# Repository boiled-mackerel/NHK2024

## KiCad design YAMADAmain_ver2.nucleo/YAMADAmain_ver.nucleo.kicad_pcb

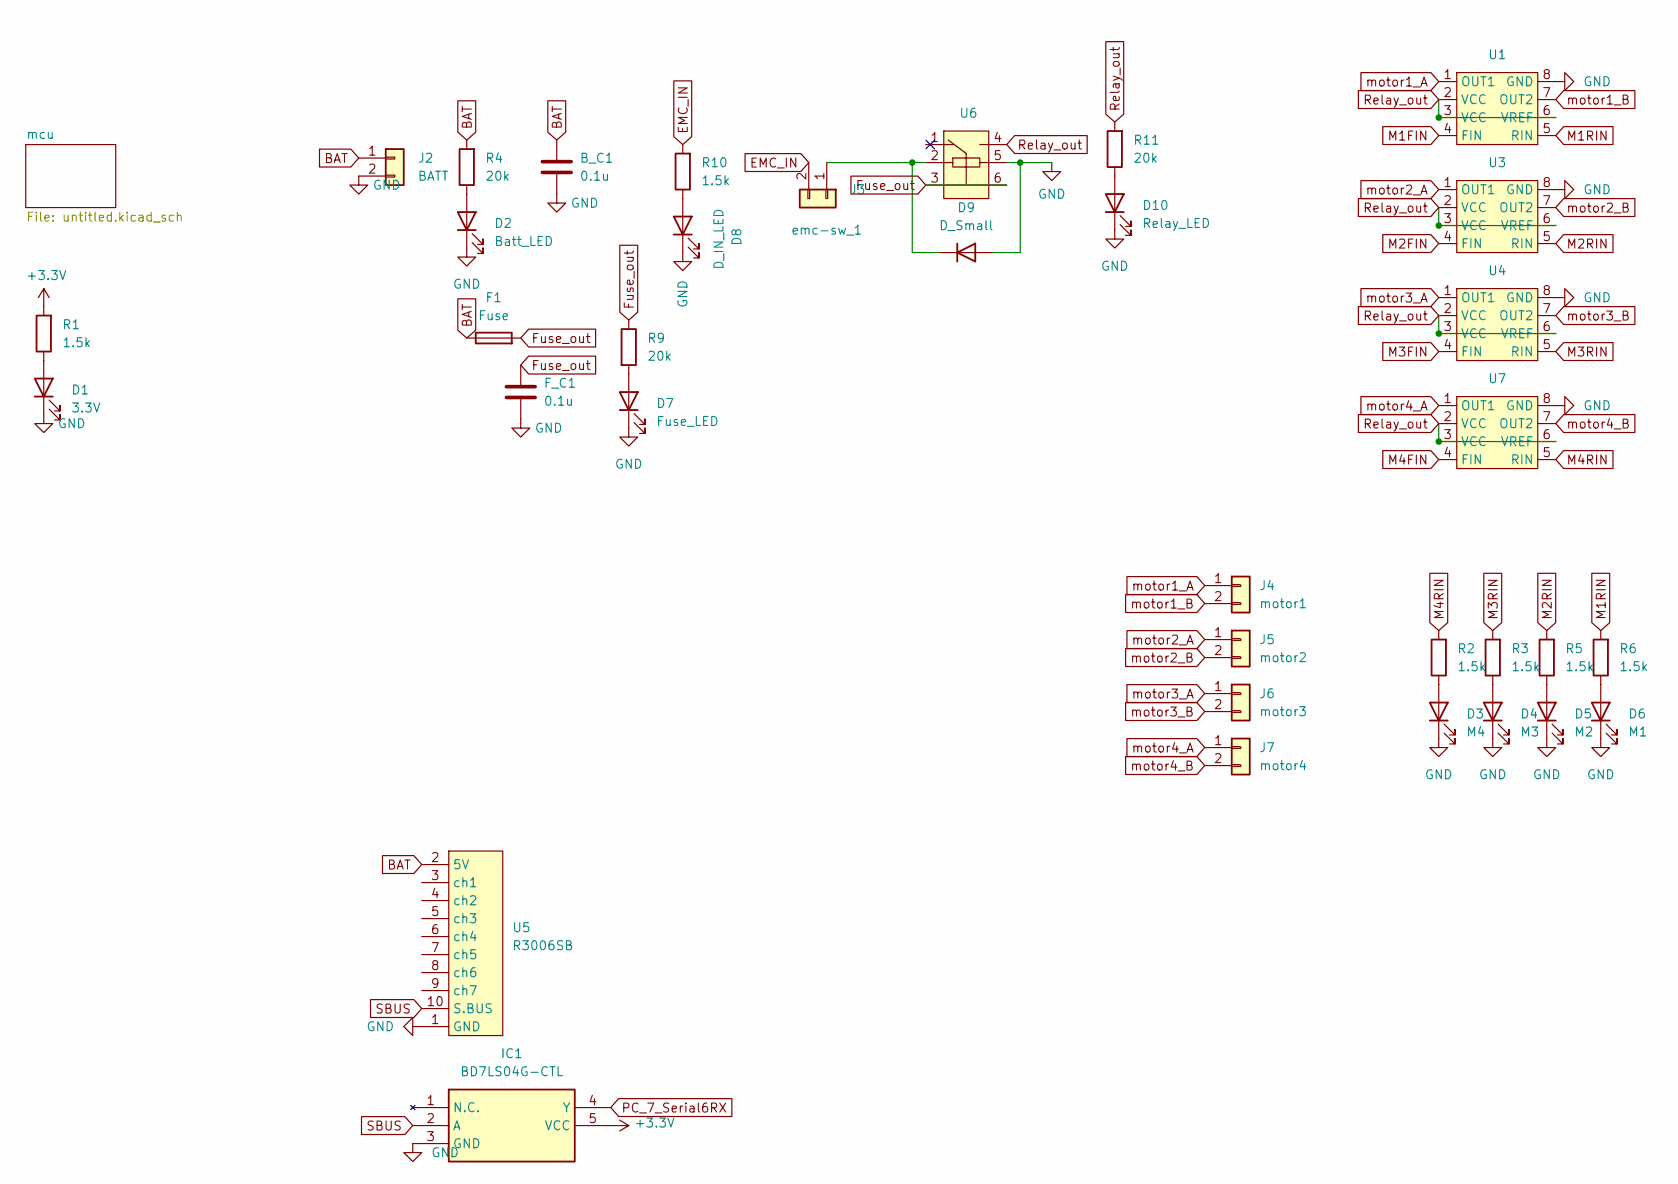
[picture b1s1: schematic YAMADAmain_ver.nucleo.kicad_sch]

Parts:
B_C1: 0.1u; C_0805_2012
D1: 3.3V; LED_D3.0mm
D2: Batt_LED; LED_D3.0mm
D3: M4; LED_D3.0mm
D4: M3; LED_D3.0mm
D5: M2; LED_D3.0mm
D6: M1; LED_D3.0mm
D7: Fuse_LED; LED_D3.0mm
D8: D_IN_LED; LED_D3.0mm
D9: D_Small; D_SOD-123
D10: Relay_LED; LED_D3.0mm
F1: Fuse; FuseHolder_Carfuse
F_C1: 0.1u; C_0805_2012Metric_Pad1.18x1.45mm_HandSolder
IC1: BD7LS04G-CTL; SOT95P280X125-5N; Manufacturer_Part_Number BD7LS04G-CTL
J2: BATT; POWER_PAD
J3: emc-sw_1; JST_XA_S02B-XASK-1_1x02_P2.50mm_Horizontal
J4: motor1; JST_GH_BM02B-GHS-TBT_1x02-1MP_P1.25mm_Vertical
J5: motor2; JST_GH_BM02B-GHS-TBT_1x02-1MP_P1.25mm_Vertical
J6: motor3; JST_GH_BM02B-GHS-TBT_1x02-1MP_P1.25mm_Vertical
J7: motor4; JST_GH_BM02B-GHS-TBT_1x02-1MP_P1.25mm_Vertical
R1, R2, R3, R5, R6, R10: 1.5k; R_Axial_DIN0207_L6.3mm_D2.5mm_P7.62mm_Horizontal
R4, R9, R11: 20k; R_Axial_DIN0207_L6.3mm_D2.5mm_P7.62mm_Horizontal
U1, U3, U4, U7: SOP8
U5: R3006SB
U6: Y14H-1C-3DS

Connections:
+3.3V: IC1.5 (VCC), R1.2; also elsewhere on the board
BAT: B_C1.1, F1.1, J2.1, R4.2, U5.2 (5V); also elsewhere on the board
EMC_IN: J3.2, R10.2; also elsewhere on the board
Fuse_out: F1.2, F_C1.1, R9.1, U6.3, U6.6
GND: B_C1.2, D1.1 (K), D2.1 (K), D3.1 (K), D4.1 (K), D5.1 (K), D6.1 (K), D7.1 (K), D8.1 (K), D9.2 (A), D10.1 (K), F_C1.2, IC1.3 (GND), J2.2, U1.8 (GND), U3.8 (GND), U4.8 (GND), U5.1 (GND), U6.5, U7.8 (GND); also elsewhere on the board
M1FIN: U1.4 (FIN); also elsewhere on the board
M1RIN: R6.2, U1.5 (RIN); also elsewhere on the board
M2FIN: U3.4 (FIN); also elsewhere on the board
M2RIN: R5.2, U3.5 (RIN); also elsewhere on the board
M3FIN: U4.4 (FIN); also elsewhere on the board
M3RIN: R3.2, U4.5 (RIN); also elsewhere on the board
M4FIN: U7.4 (FIN); also elsewhere on the board
M4RIN: R2.2, U7.5 (RIN); also elsewhere on the board
unnamed: D1.2 (A), R1.1
unnamed: D2.2 (A), R4.1
unnamed: D3.2 (A), R2.1
unnamed: D4.2 (A), R3.1
unnamed: D5.2 (A), R5.1
unnamed: D6.2 (A), R6.1
unnamed: D7.2 (A), R9.2
unnamed: D8.2 (A), R10.1
unnamed: D9.1 (K), J3.1, U6.2
unnamed: D10.2 (A), R11.1
PC_7_Serial6RX: IC1.4 (Y); also elsewhere on the board
Relay_out: R11.2, U1.2 (VCC), U1.3 (VCC), U1.6 (VREF), U3.2 (VCC), U3.3 (VCC), U3.6 (VREF), U4.2 (VCC), U4.3 (VCC), U4.6 (VREF), U6.4, U7.2 (VCC), U7.3 (VCC), U7.6 (VREF)
SBUS: IC1.2 (A), U5.10 (S.BUS)
motor1_A: J4.1, U1.1 (OUT1)
motor1_B: J4.2, U1.7 (OUT2)
motor2_A: J5.1, U3.1 (OUT1)
motor2_B: J5.2, U3.7 (OUT2)
motor3_A: J6.1, U4.1 (OUT1)
motor3_B: J6.2, U4.7 (OUT2)
motor4_A: J7.1, U7.1 (OUT1)
motor4_B: J7.2, U7.7 (OUT2)

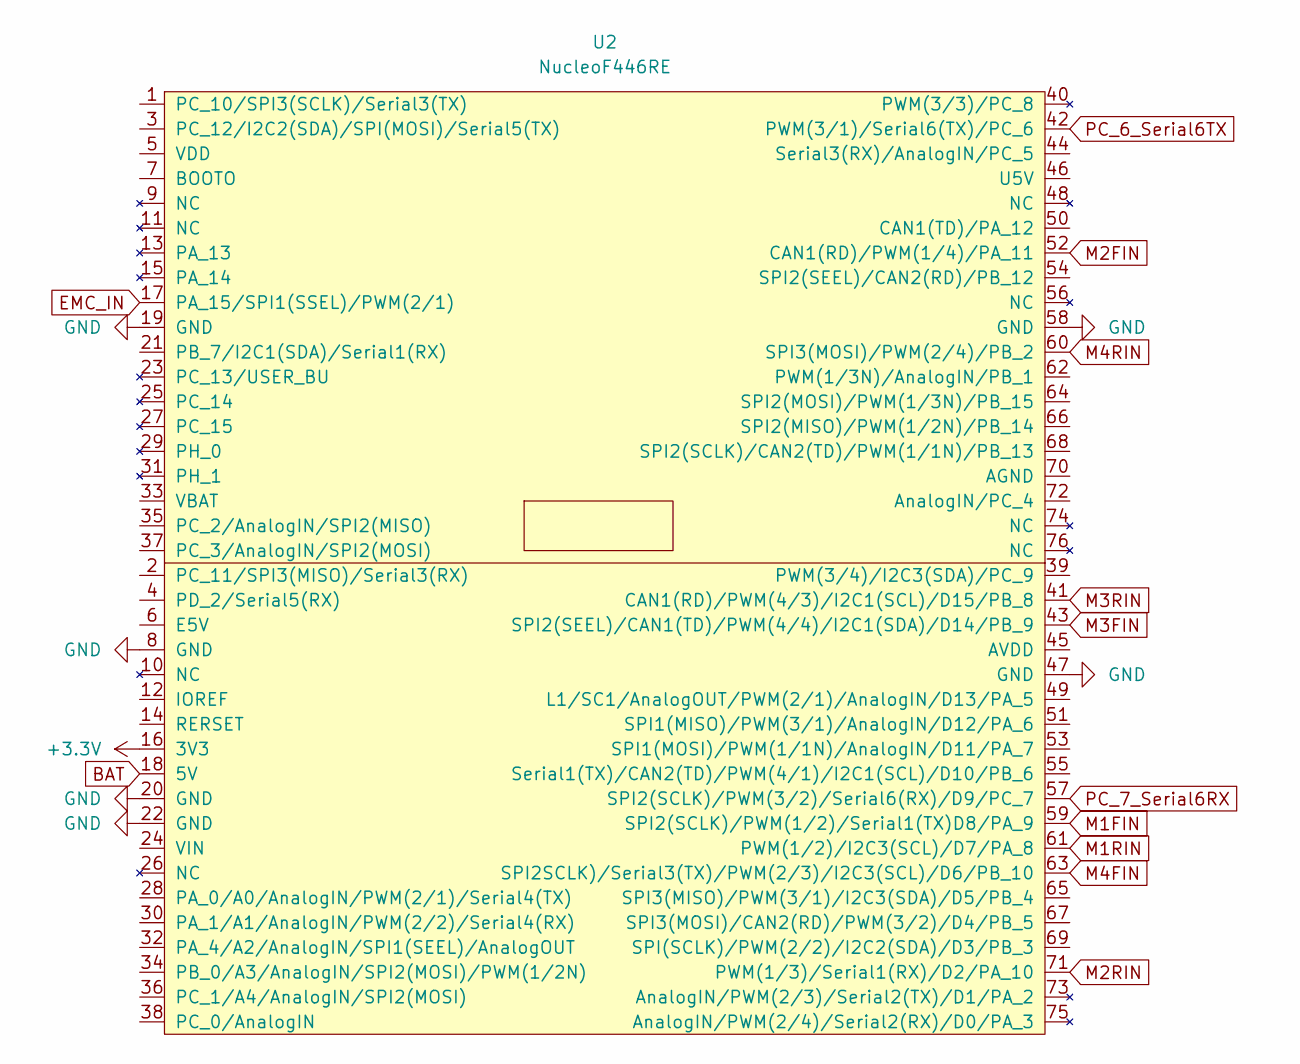
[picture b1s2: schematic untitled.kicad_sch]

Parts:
U2: NucleoF446RE; Nucleo64Board_F446RE

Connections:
+3.3V: U2.16 (3V3); also elsewhere on the board
BAT: U2.18 (5V); also elsewhere on the board
EMC_IN: U2.17 (PA_15/SPI1(SSEL)/PWM(2/1)); also elsewhere on the board
GND: U2.8 (GND), U2.19 (GND), U2.20 (GND), U2.22 (GND), U2.47 (GND), U2.58 (GND); also elsewhere on the board
M1FIN: U2.59 (SPI2(SCLK)/PWM(1/2)/Serial1(TX)D8/PA_9); also elsewhere on the board
M1RIN: U2.61 (PWM(1/2)/I2C3(SCL)/D7/PA_8); also elsewhere on the board
M2FIN: U2.52 (CAN1(RD)/PWM(1/4)/PA_11); also elsewhere on the board
M2RIN: U2.71 (PWM(1/3)/Serial1(RX)/D2/PA_10); also elsewhere on the board
M3FIN: U2.43 (SPI2(SEEL)/CAN1(TD)/PWM(4/4)/I2C1(SDA)/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); also elsewhere on the board
M3RIN: U2.41 (CAN1(RD)/PWM(4/3)/I2C1(SCL)/D15/PB_8); also elsewhere on the board
M4FIN: U2.63 (SPI2SCLK)/Serial3(TX)/PWM(2/3)/I2C3(SCL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); also elsewhere on the board
M4RIN: U2.60 (SPI3(MOSI)/PWM(2/4)/PB_2); also elsewhere on the board
PC_6_Serial6TX: U2.42 (PWM(3/1)/Serial6(TX)/PC_6)
PC_7_Serial6RX: U2.57 (SPI2(SCLK)/PWM(3/2)/Serial6(RX)/D9/PC_7); also elsewhere on the board

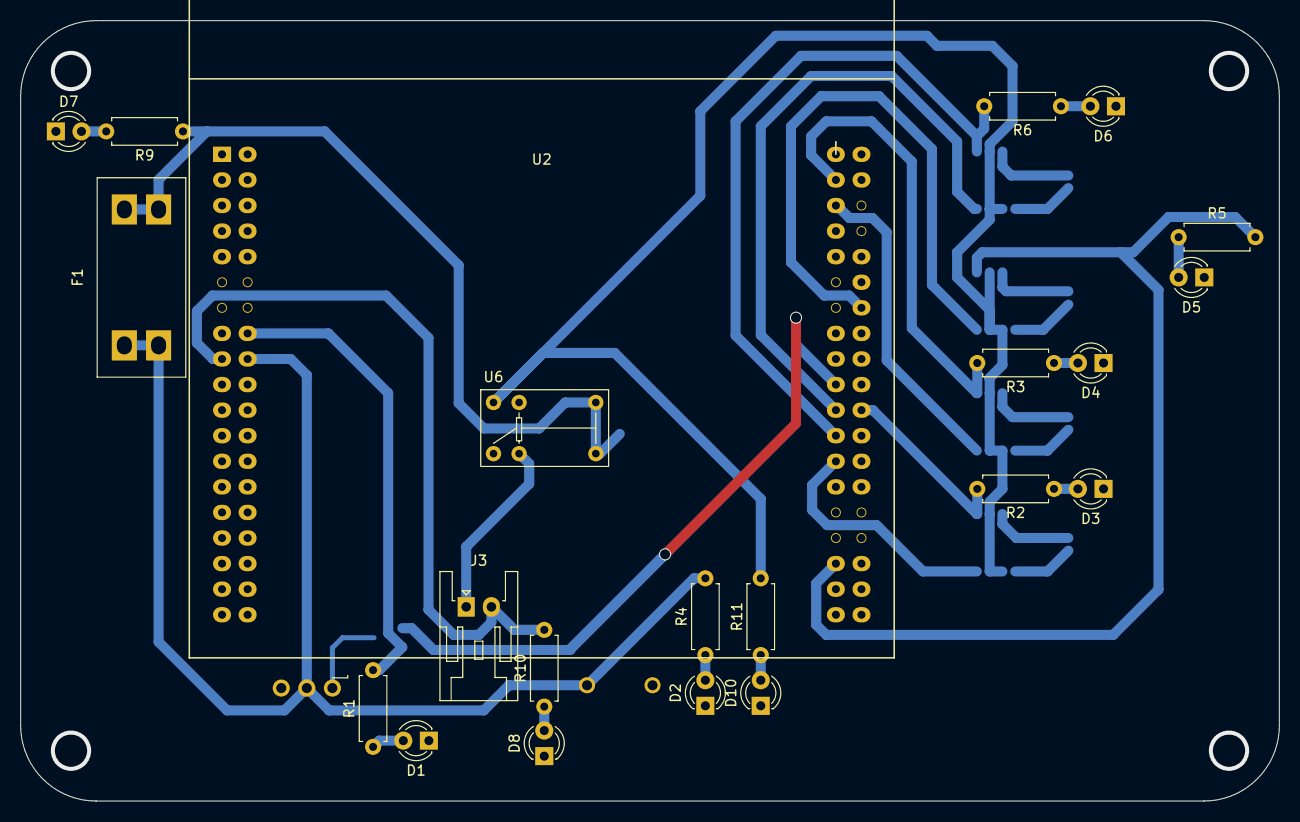
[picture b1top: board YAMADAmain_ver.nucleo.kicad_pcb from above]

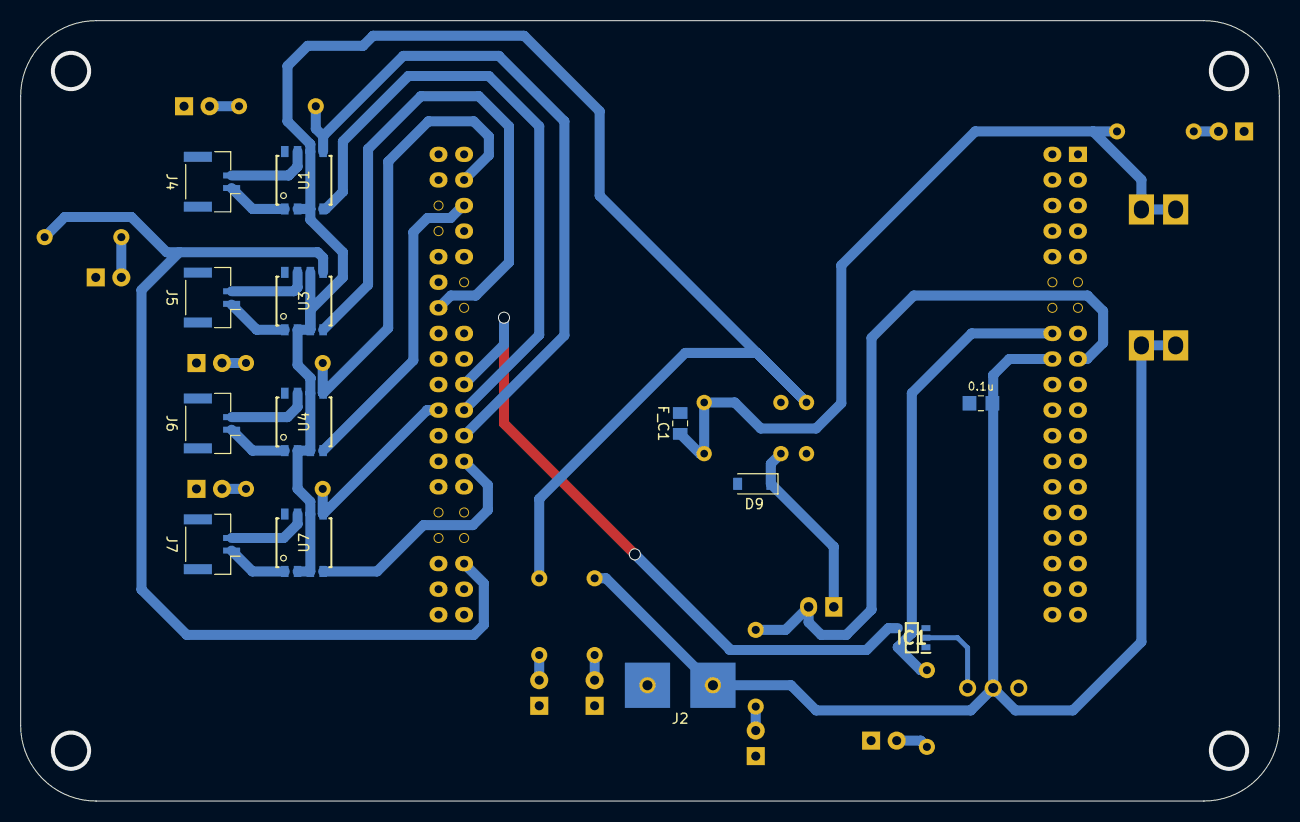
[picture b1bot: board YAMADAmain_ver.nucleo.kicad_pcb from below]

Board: 2 copper layers, 125.0 x 77.5 mm, 36 parts (13 on the bottom side), 34 nets.

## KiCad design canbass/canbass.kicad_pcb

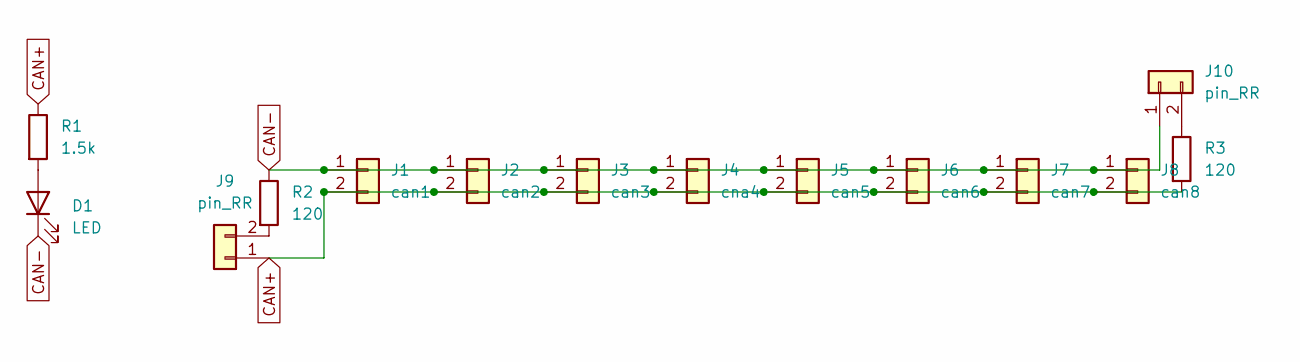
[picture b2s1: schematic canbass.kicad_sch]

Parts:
D1: LED; LED_0603_1608Metric_Pad1.05x0.95mm_HandSolder
J1: can1; JST_GH_SM02B-GHS-TB_1x02-1MP_P1.25mm_Horizontal
J2: can2; JST_GH_SM02B-GHS-TB_1x02-1MP_P1.25mm_Horizontal
J3: can3; JST_GH_SM02B-GHS-TB_1x02-1MP_P1.25mm_Horizontal
J4: cna4; JST_GH_SM02B-GHS-TB_1x02-1MP_P1.25mm_Horizontal
J5: can5; JST_GH_SM02B-GHS-TB_1x02-1MP_P1.25mm_Horizontal
J6: can6; JST_GH_SM02B-GHS-TB_1x02-1MP_P1.25mm_Horizontal
J7: can7; JST_GH_SM02B-GHS-TB_1x02-1MP_P1.25mm_Horizontal
J8: can8; JST_GH_SM02B-GHS-TB_1x02-1MP_P1.25mm_Horizontal
J9, J10: pin_RR; PinSocket_1x02_P2.54mm_Vertical
R1: 1.5k; R_0805_2012Metric_Pad1.20x1.40mm_HandSolder
R2: 120; R_0805_2012Metric_Pad1.20x1.40mm_HandSolder
R3: 120; R_0805_2012Metric

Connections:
CAN+: J1.2, J2.2, J3.2, J4.2, J5.2, J6.2, J7.2, J8.2, J9.1, R1.1, R3.2
CAN-: D1.1 (K), J1.1, J2.1, J3.1, J4.1, J5.1, J6.1, J7.1, J8.1, J10.1, R2.1
unnamed: D1.2 (A), R1.2
unnamed: J9.2, R2.2
unnamed: J10.2, R3.1

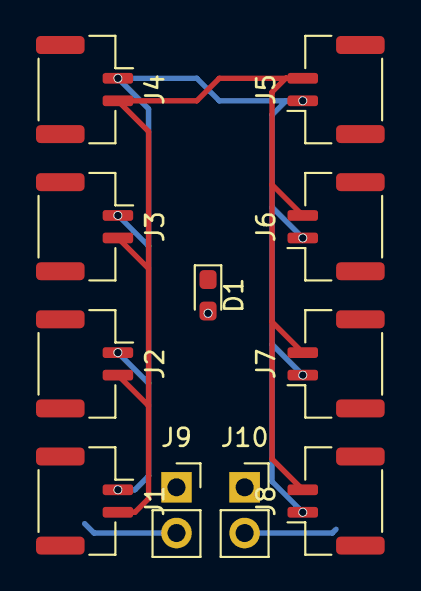
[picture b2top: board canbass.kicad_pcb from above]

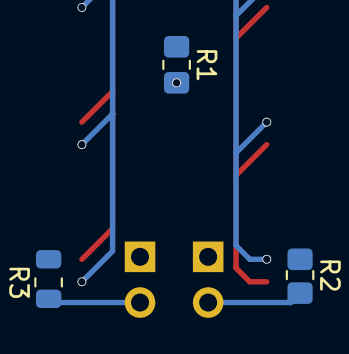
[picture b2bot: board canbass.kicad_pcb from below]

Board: 2 copper layers, 14 parts (3 on the bottom side), 5 nets.

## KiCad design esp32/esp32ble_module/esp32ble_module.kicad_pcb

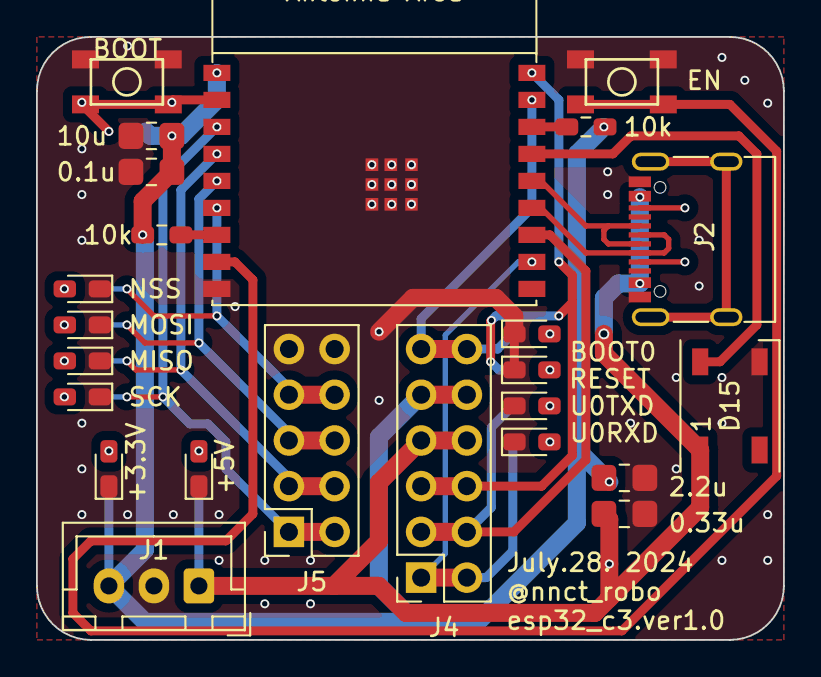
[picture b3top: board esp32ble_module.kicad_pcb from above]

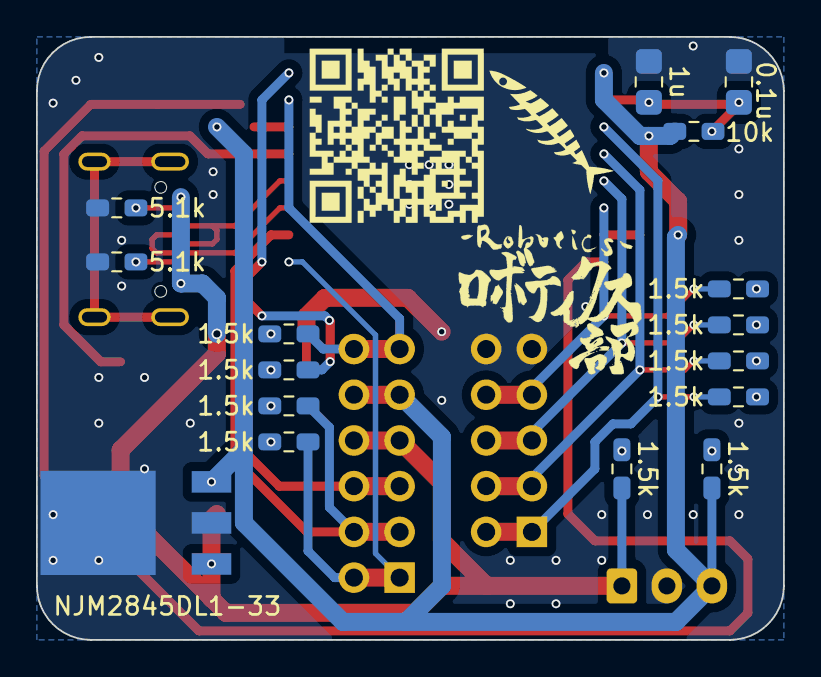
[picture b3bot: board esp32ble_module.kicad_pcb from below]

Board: 2 copper layers, 41.5 x 33.5 mm, 40 parts (16 on the bottom side), 30 nets.

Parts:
C1: 0.33u; C_0805_2012
C2, C6: 0.1u; C_0805_2012
C3: 1u; C_0805_2012
C4: 2.2u; C_0805_2012
C5: 10u; C_0805_2012
D1: +5V; LED_0603_1608
D2: +3.3V; LED_0603_1608
D3: SCK; LED_0603_1608
D4: NSS; LED_0603_1608
D5: MISO; LED_0603_1608
D6: MOSI; LED_0603_1608
D7: U0RXD; LED_0603_1608
D8: U0TXD; LED_0603_1608
D9: BOOT0; LED_0603_1608
D10: RESET; LED_0603_1608
D15: WS2812B; LED_WS2812B_PLCC4_5.0x5.0mm_P3.2mm
J1: power; JST_XH_B3B-XH-A_1x03_P2.50mm_Vertical
J2: USB_C_Receptacle_USB2.0; USB_C_Receptacle_G-Switch_GT-USB-7010ASV
J4: Conn_02x06_Counter_Clockwise; PinSocket_2x06_P2.54mm_Vertical
J5: Conn_02x05_Counter_Clockwise; PinSocket_2x05_P2.54mm_Vertical
R1, R2, R3, R4, R5, R6, R7, R8, R9, R10: 1.5k; R_0603_1608
R15, R16: 5.1k; R_0603_1608
R17, R20, R21: 10k; R_0603_1608
U2: NJM2845DL1-33
U5, U7: SW_DP3T; tact_sw_smd_skrpabe10
U6: ESP32-C3-WROOM-02

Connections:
+3.3V: C4.1, C5.2, C6.2, J1.3, J4.9, J4.10, R2.1, R17.1, R20.2, R21.2, U2.3 (Vout), U6.1 (3V3)
+5V: C1.1, D15.1 (VDD), J1.1, J2.A4 (VBUS), J2.A9 (VBUS), J2.B4 (VBUS), J2.B9 (VBUS), J4.7, J4.8, R1.1, U2.1 (Vin)
BOOT0: J4.11, J4.12, R9.1, U6.17 (GPIO1/ADC1_CH1/XTAL_32K_N)
D+: J2.A6 (D+), J2.B6 (D+), U6.14 (GPIO19/USB_D+)
D-: J2.A7 (D-), J2.B7 (D-), U6.13 (GPIO18/USB_D-)
GND: C1.2, C2.2, C3.2, C4.2, C5.1, C6.1, D1.1 (K), D2.1 (K), D3.1 (K), D4.1 (K), D5.1 (K), D6.1 (K), D7.1 (K), D8.1 (K), D9.1 (K), D10.1 (K), D15.3 (VSS), J1.2, J2.A1 (GND), J2.A12 (GND), J2.B1 (GND), J2.B12 (GND), J5.9, J5.10, R15.2, R16.2, U2.2 (GND), U5.1, U5.3, U6.9 (GND), U6.19 (GND), U7.2, U7.4
LED_DIN: D15.4 (DIN), U6.15 (GPIO3/ADC1_CH3)
MISO: J5.3, J5.4, R5.1, U6.4 (GPIO5/ADC2_CH0)
MOSI: J5.5, J5.6, R6.1, U6.5 (GPIO6)
NSS: J5.7, J5.8, R4.1, U6.6 (GPIO7)
unnamed: D1.2 (A), R1.2
unnamed: D2.2 (A), R2.2
unnamed: D3.2 (A), R3.2
unnamed: D4.2 (A), R4.2
unnamed: D5.2 (A), R5.2
unnamed: D6.2 (A), R6.2
unnamed: D7.2 (A), R7.2
unnamed: D8.2 (A), R8.2
unnamed: D9.2 (A), R9.2
unnamed: D10.2 (A), R10.2
unnamed: J2.A5 (CC1), R15.1
unnamed: J2.B5 (CC2), R16.1
unnamed: C2.1, C3.1, R17.2, U5.2, U5.4, U6.2 (EN/CHIP_PU)
unnamed: R20.1, U6.16 (GPIO2/ADC1_CH2)
unnamed: R21.1, U6.7 (GPIO8)
unnamed: U6.8 (GPIO9), U7.1, U7.3
RESET: J4.5, J4.6, R10.1, U6.18 (GPIO0/ADC1_CH0/XTAL_32K_P)
SCK: J5.1, J5.2, R3.1, U6.3 (GPIO4/ADC1_CH4)
U0RXD: J4.1, J4.2, R7.1, U6.11 (GPIO20/U0RXD)
U0TXD: J4.3, J4.4, R8.1, U6.12 (GPIO21/U0TXD)

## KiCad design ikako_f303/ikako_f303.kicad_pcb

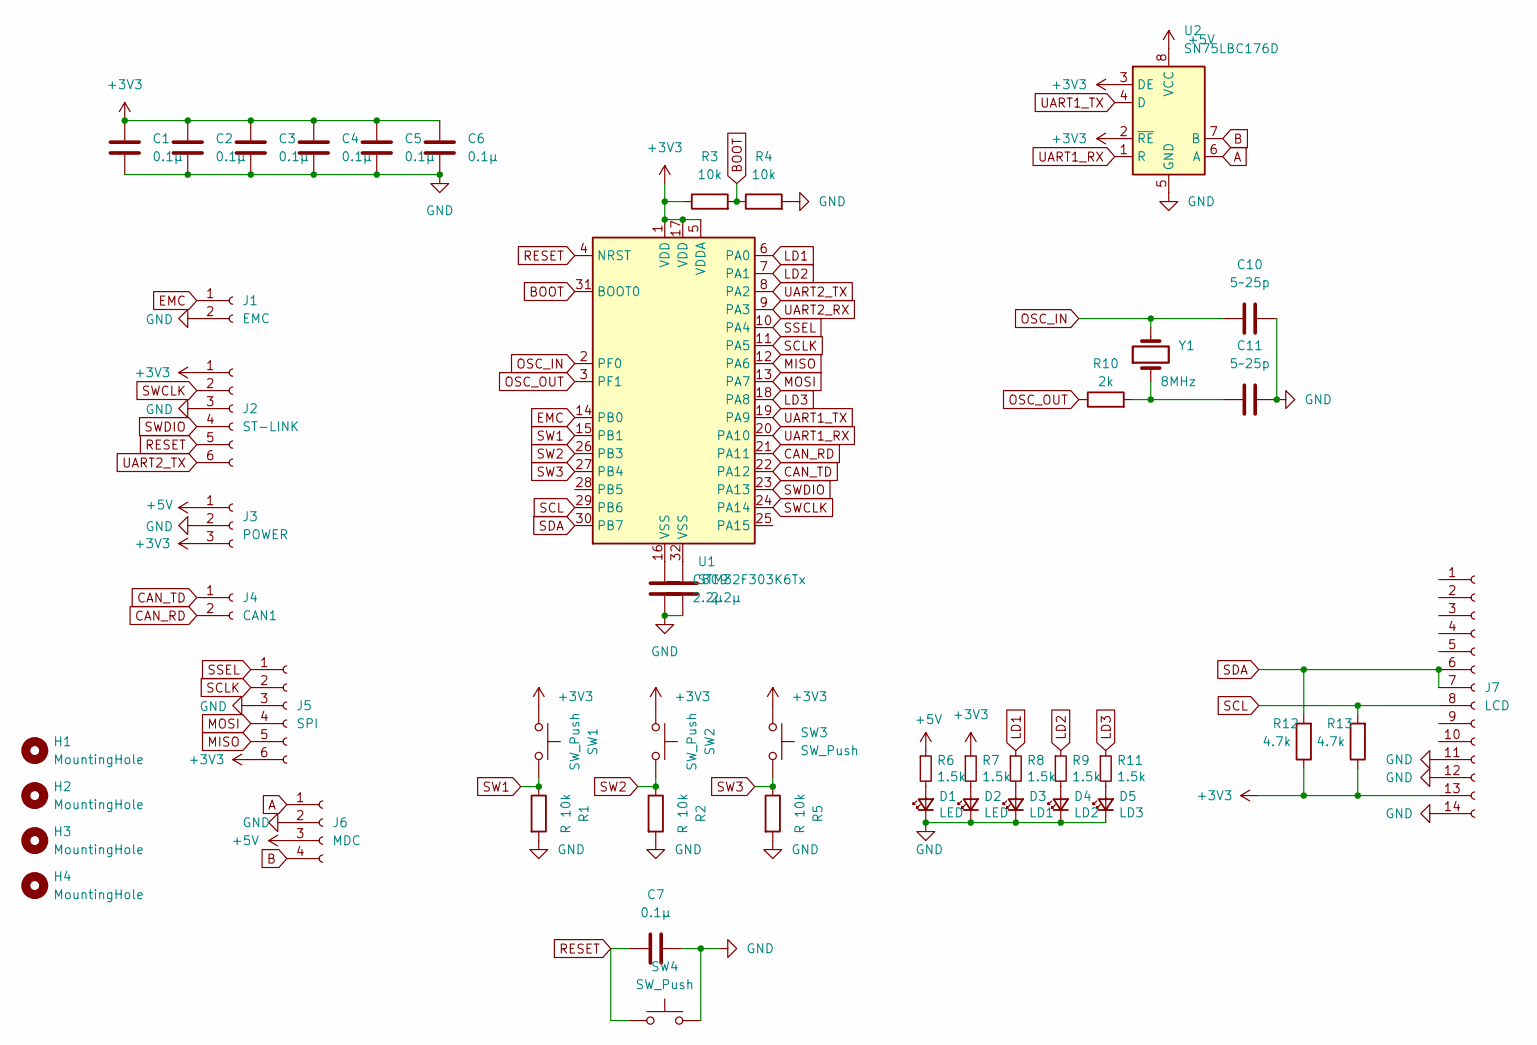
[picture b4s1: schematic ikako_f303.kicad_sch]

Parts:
C1, C2, C3, C4, C5, C6, C7: 0.1µ; C_0504_1310Metric_Pad0.83x1.28mm_HandSolder
C8, C9: 2.2µ; C_1206_3216Metric_Pad1.33x1.80mm_HandSolder
C10, C11: 5~25p; C_0805_2012Metric_Pad1.18x1.45mm_HandSolder
D1, D2: LED; LED_0603_1608Metric_Pad1.05x0.95mm_HandSolder
D3: LD1; LED_0603_1608Metric_Pad1.05x0.95mm_HandSolder
D4: LD2; LED_0603_1608Metric_Pad1.05x0.95mm_HandSolder
D5: LD3; LED_0603_1608Metric_Pad1.05x0.95mm_HandSolder
H1, H2, H3, H4: MountingHole; MountingHole_3.2mm_M3_Pad_Via
J1: EMC; JST_XA_S02B-XASK-1_1x02_P2.50mm_Horizontal
J2: ST-LINK; JST_XA_S06B-XASK-1_1x06_P2.50mm_Horizontal
J3: POWER; JST_XA_S03B-XASK-1_1x03_P2.50mm_Horizontal
J4: CAN1; JST_XA_S02B-XASK-1_1x02_P2.50mm_Horizontal
J5: SPI; PinSocket_1x06_P2.54mm_Horizontal
J6: MDC; JST_XA_S04B-XASK-1_1x04_P2.50mm_Horizontal
J7: LCD; PinSocket_1x14_P2.54mm_Vertical
R1, R2, R5: R 10k; R_0805_2012Metric_Pad1.20x1.40mm_HandSolder
R3, R4: 10k; R_0805_2012Metric_Pad1.20x1.40mm_HandSolder
R6, R7, R8, R9, R11: 1.5k; R_0805_2012Metric_Pad1.20x1.40mm_HandSolder
R10: 2k; R_0805_2012Metric_Pad1.20x1.40mm_HandSolder
R12, R13: 4.7k; R_0805_2012Metric_Pad1.20x1.40mm_HandSolder
SW1, SW2, SW3, SW4: SW_Push; SW_PUSH_6mm
U1: STM32F303K6Tx; LQFP-32_7x7mm_P0.8mm
U2: SN75LBC176D; DIP-8_W7.62mm
Y1: 8MHz; Resonator-2Pin_W10.0mm_H5.0mm

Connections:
+3V3: C1.1, C2.1, C3.1, C4.1, C5.1, C6.1, J2.1, J3.3, J5.6, J7.13, R3.1, R7.1, R12.1, R13.1, SW1.1, SW2.1, SW3.1, U1.1 (VDD), U1.5 (VDDA), U1.17 (VDD), U2.2 (~RE), U2.3 (DE)
+5V: J3.1, J6.3, R6.1, U2.8 (VCC)
A: J6.1, U2.6 (A)
B: J6.4, U2.7 (B)
BOOT: R3.2, R4.1, U1.31 (BOOT0)
CAN_RD: J4.2, U1.21 (PA11)
CAN_TD: J4.1, U1.22 (PA12)
EMC: J1.1, U1.14 (PB0)
GND: C1.2, C2.2, C3.2, C4.2, C5.2, C6.2, C7.2, C8.2, C9.2, C10.2, C11.2, D1.1 (K), D2.1 (K), D3.1 (K), D4.1 (K), D5.1 (K), J1.2, J2.3, J3.2, J5.3, J6.2, J7.11, J7.12, J7.14, R1.2, R2.2, R4.2, R5.2, SW4.2, U2.5 (GND)
LD1: R8.1, U1.6 (PA0)
LD2: R9.1, U1.7 (PA1)
LD3: R11.1, U1.18 (PA8)
MISO: J5.5, U1.12 (PA6)
MOSI: J5.4, U1.13 (PA7)
unnamed: C8.1, U1.16 (VSS)
unnamed: C9.1, U1.32 (VSS)
unnamed: C11.1, R10.2, Y1.1
unnamed: D1.2 (A), R6.2
unnamed: D2.2 (A), R7.2
unnamed: D3.2 (A), R8.2
unnamed: D4.2 (A), R9.2
unnamed: D5.2 (A), R11.2
OSC_IN: C10.1, U1.2 (PF0), Y1.2
OSC_OUT: R10.1, U1.3 (PF1)
RESET: C7.1, J2.5, SW4.1, U1.4 (NRST)
SCL: J7.8, R13.2, U1.29 (PB6)
SCLK: J5.2, U1.11 (PA5)
SDA: J7.6, J7.7, R12.2, U1.30 (PB7)
SSEL: J5.1, U1.10 (PA4)
SW1: R1.1, SW1.2, U1.15 (PB1)
SW2: R2.1, SW2.2, U1.26 (PB3)
SW3: R5.1, SW3.2, U1.27 (PB4)
SWCLK: J2.2, U1.24 (PA14)
SWDIO: J2.4, U1.23 (PA13)
UART1_RX: U1.20 (PA10), U2.1 (R)
UART1_TX: U1.19 (PA9), U2.4 (D)
UART2_RX: U1.9 (PA3)
UART2_TX: J2.6, U1.8 (PA2)

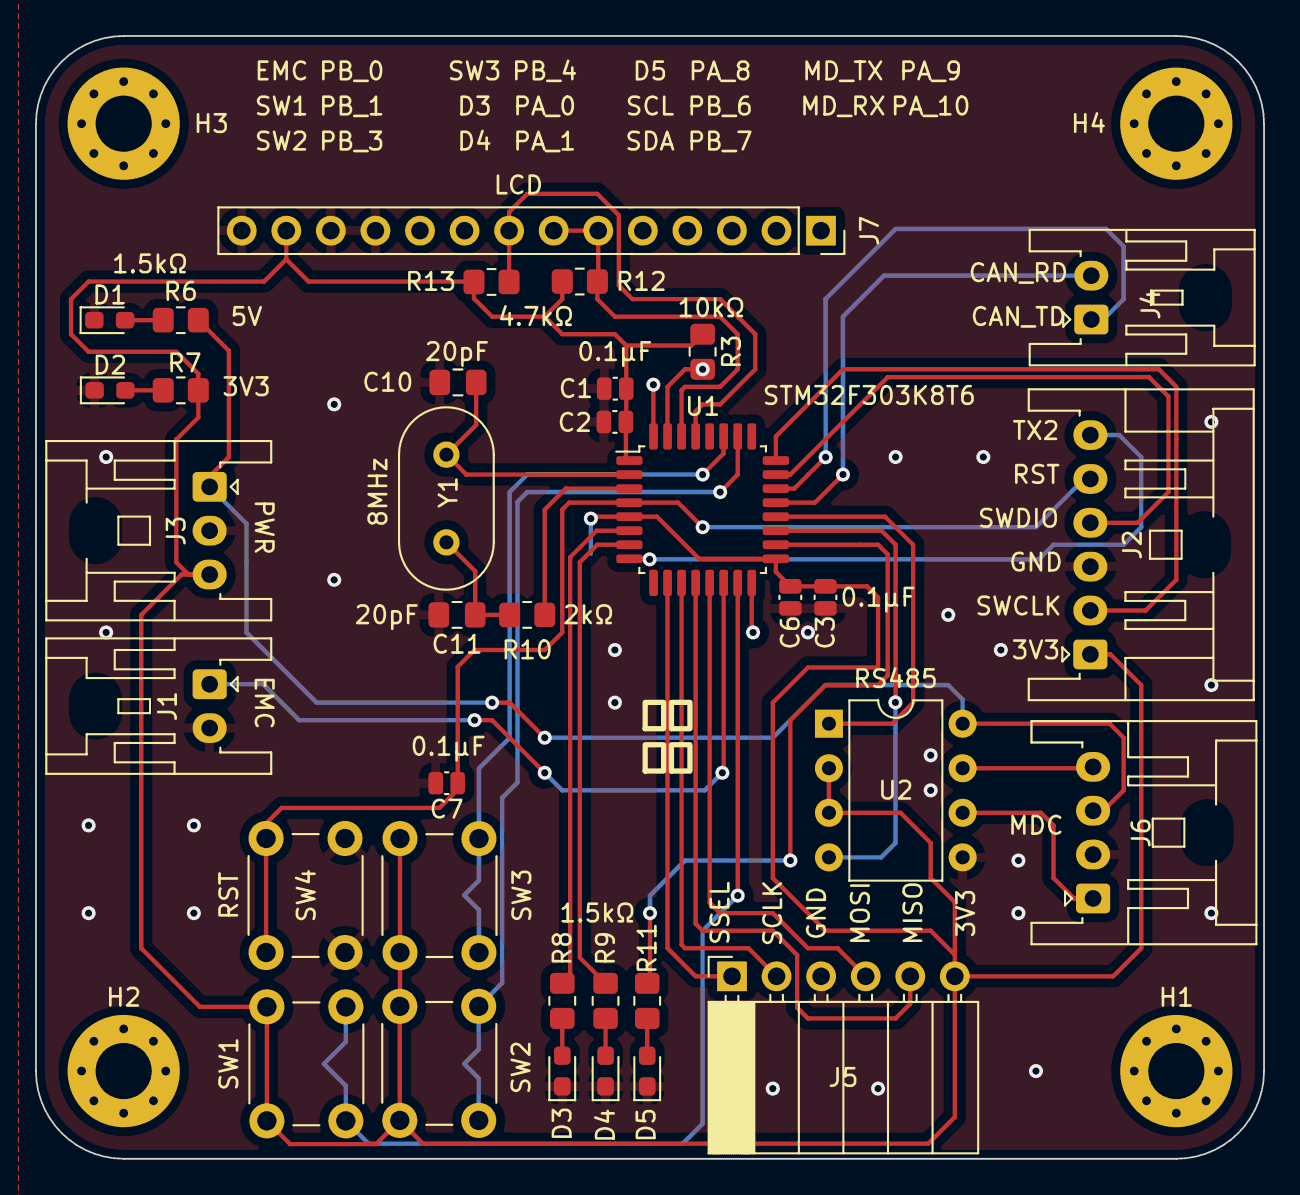
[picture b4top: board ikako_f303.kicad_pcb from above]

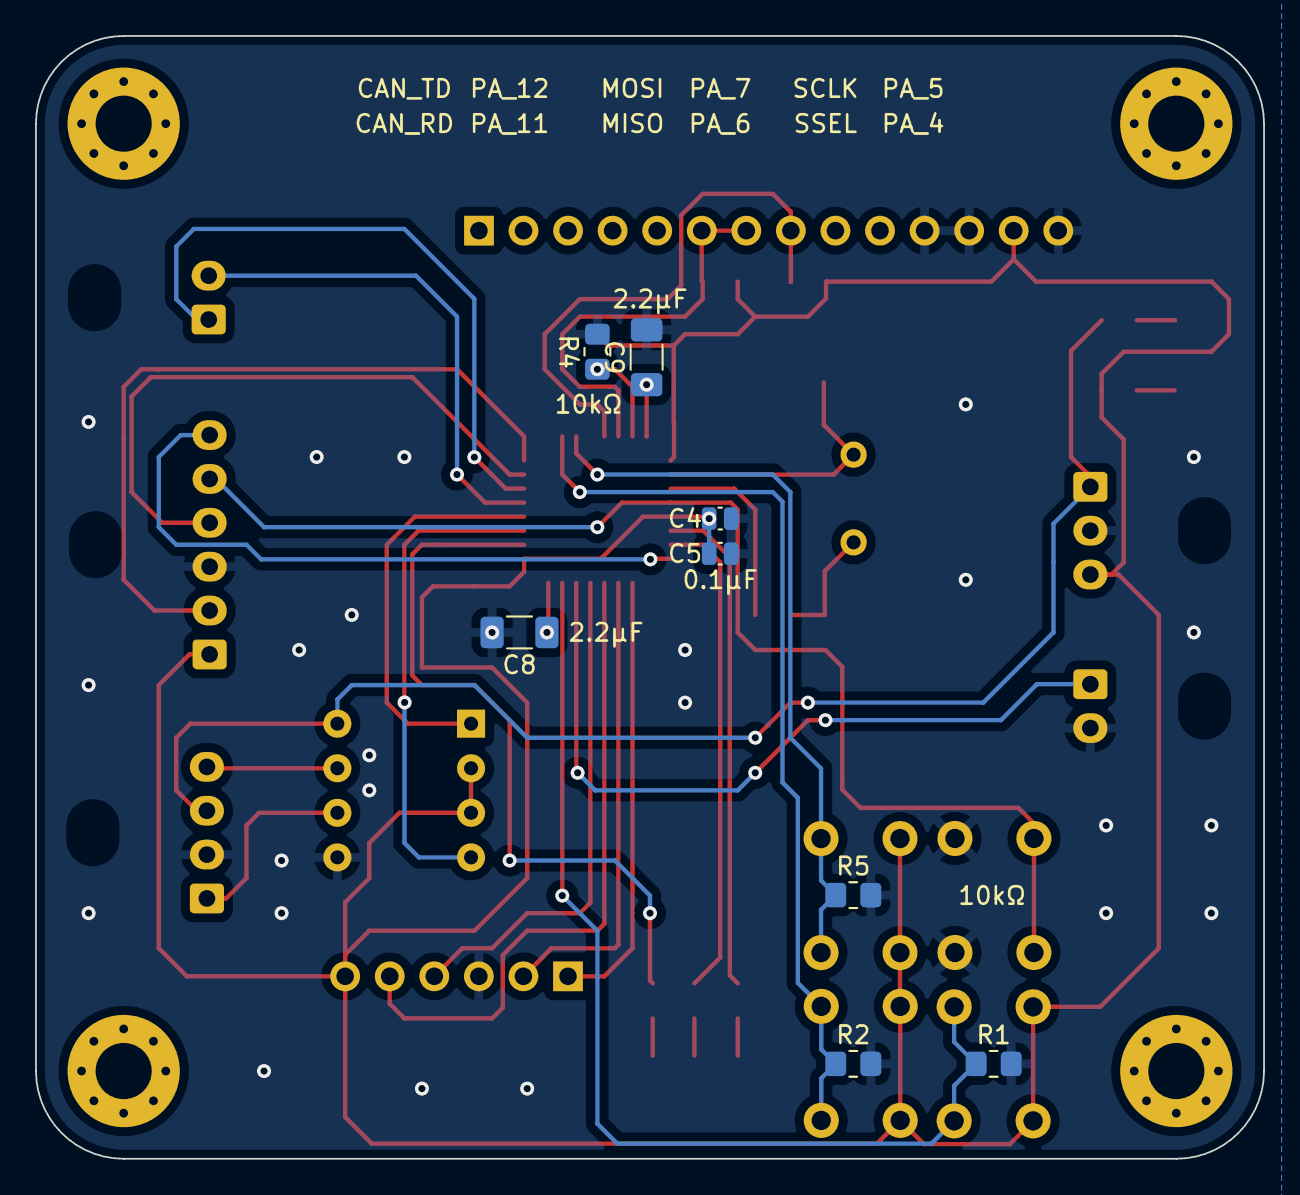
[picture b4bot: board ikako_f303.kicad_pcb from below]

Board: 2 copper layers, 70.0 x 64.0 mm, 47 parts (8 on the bottom side), 37 nets.

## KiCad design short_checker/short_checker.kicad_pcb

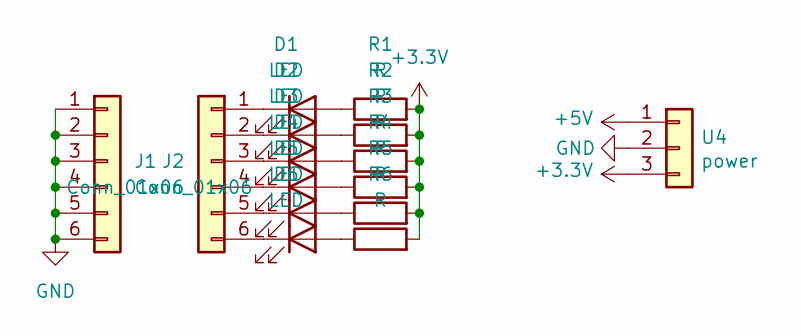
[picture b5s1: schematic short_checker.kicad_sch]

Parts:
D1, D2, D3, D4, D5, D6: LED; LED_D3.0mm
J1, J2: Conn_01x06; PinHeader_1x06_P2.54mm_Vertical
R1, R2, R3, R4, R5, R6: R; R_Axial_DIN0207_L6.3mm_D2.5mm_P7.62mm_Horizontal
U4: power; JST_XH_B3B-XH-A_1x03_P2.50mm_Vertical

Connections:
+3.3V: R1.2, R2.2, R3.2, R4.2, R5.2, R6.2; also elsewhere on the board
GND: J1.1, J1.2, J1.3, J1.4, J1.5, J1.6; also elsewhere on the board
unnamed: D1.2 (A), R1.1
unnamed: D1.1 (K), J2.1
unnamed: D2.2 (A), R2.1
unnamed: D2.1 (K), J2.2
unnamed: D3.2 (A), R3.1
unnamed: D3.1 (K), J2.3
unnamed: D4.2 (A), R4.1
unnamed: D4.1 (K), J2.4
unnamed: D5.2 (A), R5.1
unnamed: D5.1 (K), J2.5
unnamed: D6.2 (A), R6.1
unnamed: D6.1 (K), J2.6

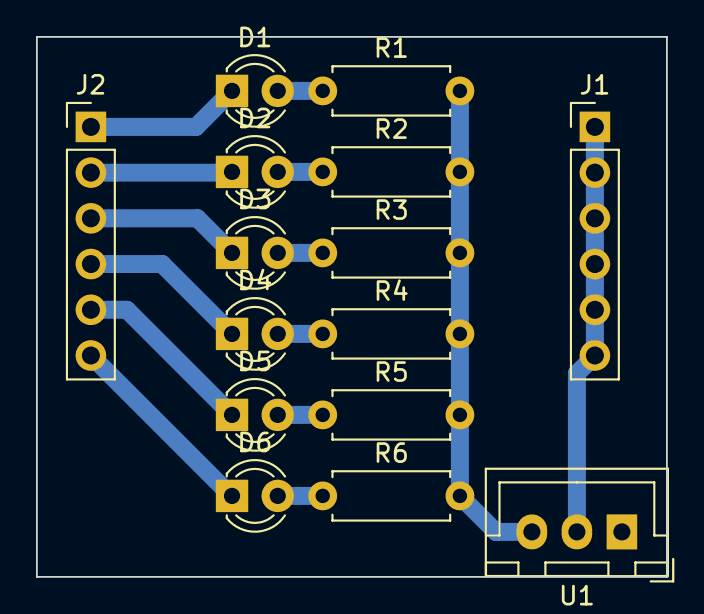
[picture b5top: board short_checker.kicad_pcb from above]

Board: 2 copper layers, 35.0 x 30.0 mm, 15 parts (0 on the bottom side), 14 nets.

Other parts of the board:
U1: power; JST_XH_B3B-XH-A_1x03_P2.50mm_Vertical

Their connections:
+3.3V: U1.3; also elsewhere on the board
GND: U1.2; also elsewhere on the board
